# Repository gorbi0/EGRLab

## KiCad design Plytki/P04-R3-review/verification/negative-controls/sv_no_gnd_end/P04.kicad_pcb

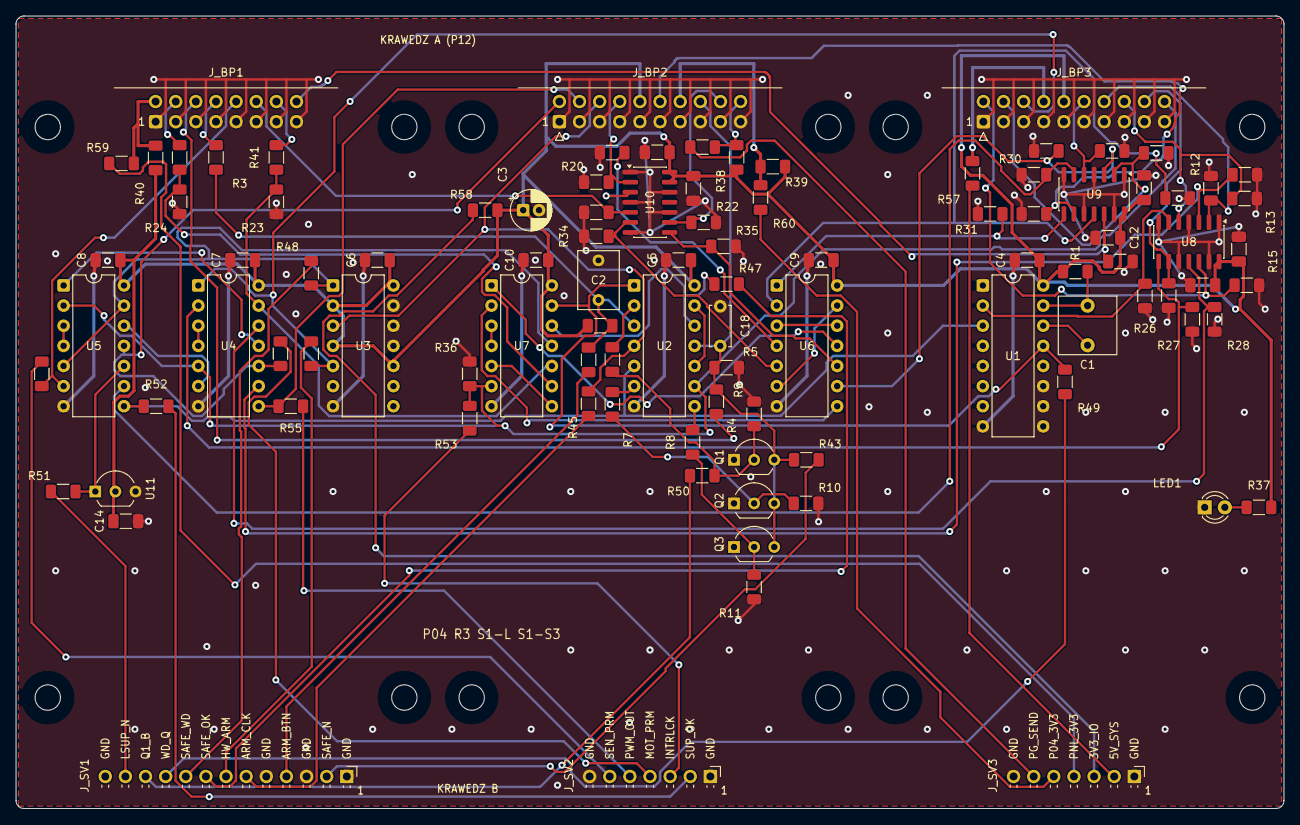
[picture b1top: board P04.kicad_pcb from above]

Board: 2 copper layers, 160.0 x 100.0 mm, 112 parts (0 on the bottom side), 86 nets.

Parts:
C1: 1u; C_WIMA_MKS2_1u100V_L7.2_W7.2_P5
C2: 1u; C_Rect_L7.2mm_W5.0mm_P5.00mm
C3: 10u; CP_Radial_D5.0mm_P2.00mm
C4, C5, C6, C7, C8, C9, C10, C11, C12, C13, C14, C15, C16, C17: 100n; C_1206_3216Metric_Pad1.33x1.80mm_HandSolder
C18: 1n; C_Disc_D5.0mm_W2.5mm_P5.00mm
H1, H2, H3, H4, H5, H6, H7, H8, H9, H10, H11, H12: M3 NPTH
J_BP1: J_BP1; IDC-Header_2x08_P2.54mm_Horizontal
J_BP2: J_BP2; IDC-Header_2x10_P2.54mm_Horizontal
J_BP3: J_BP3; IDC-Header_2x10_P2.54mm_Horizontal
J_SV1: J_SV1 SERWIS 1x13; PinHeader_1x13_P2.54mm_Horizontal
J_SV2: J_SV2 SERWIS 1x7; PinHeader_1x07_P2.54mm_Horizontal
J_SV3: J_SV3 SERWIS 1x7; PinHeader_1x07_P2.54mm_Horizontal
LED1: POWER; LED_D3.0mm
Q1, Q2, Q3: 2N3904; TO-92_Inline_Wide
R1: 220K; R_1206_3216Metric_Pad1.30x1.75mm_HandSolder
R2, R4, R6, R7, R8, R12, R13, R14, R15, R16, R17, R18, R19, R20, R21, R22, R23, R24, R25, R29, R31, R32, R33, R34, R35, R36, R43, R44: 10K; R_1206_3216Metric_Pad1.30x1.75mm_HandSolder
R3, R37, R38, R39, R41, R42, R45, R46, R47, R48, R49, R50, R51, R52, R53, R54, R55, R56, R57, R58, R59, R60, R61: 1K; R_1206_3216Metric_Pad1.30x1.75mm_HandSolder
R5, R9, R10, R11, R28, R30: 100K; R_1206_3216Metric_Pad1.30x1.75mm_HandSolder
R26, R27: 47K; R_1206_3216Metric_Pad1.30x1.75mm_HandSolder
R40: 100R; R_1206_3216Metric_Pad1.30x1.75mm_HandSolder
U1: CD74HC123E; DIP-16_W7.62mm
U2: SN74HC14N; DIP-14_W7.62mm
U3: SN74HC74N; DIP-14_W7.62mm
U4, U5, U6, U7: SN74HC08N; DIP-14_W7.62mm
U8, U9, U10: 74LVC125AD; SOIC-14_3.9x8.7mm_P1.27mm
U11: MCP100-300DI/TO; TO-92_Inline_Wide

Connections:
3V3_IO: C3.1, C4.1, C5.1, C6.1, C7.1, C8.1, C9.1, C10.1, C11.1, C12.1, C13.1, C14.1, C15.1, C16.1, C17.1, J_BP2.10, J_BP3.10, R1.1, R2.1, R37.1, R38.1, R39.1, R40.1, R58.1, U1.16, U2.14, U3.2, U3.4, U3.10, U3.14, U4.14, U5.14, U6.14, U7.14, U8.14, U9.14, U10.13, U10.14, U11.2
5V_SYS: J_BP3.8, R57.1
/ILK/MECH_KEY: U7.5, U7.8
/ILK/MECH_OK_P04: R24.1, R42.2, U7.9
/ILK/MODULES_OK: U7.3, U7.4
/ILK/OK_A: U6.3, U6.12
/ILK/OK_AB: U6.11, U7.1
/ILK/OK_B: U6.6, U6.13
/ILK/OK_C: U6.8, U7.2
/LED_PWR: LED1.2, R37.2
/OUT/ARM_BOTH: U4.3, U4.4
/OUT/MOTOR_REQ: U4.6, U5.12
/OUT/SENSOR_INTERLOCK: U5.3, U5.4
/OUT/SENSOR_KEY: U4.11, U5.1
/SERWIS/SRV_3V3_IO: J_SV3.3, R58.2
/SERWIS/SRV_5V_SYS: J_SV3.2, R57.2
/SERWIS/SRV_ARM_BUTTON_N: J_SV1.4, R44.2
/SERWIS/SRV_ARM_CLK: J_SV1.6, R45.2
/SERWIS/SRV_HW_ARMED: J_SV1.7, R46.2
/SERWIS/SRV_INTERLOCK: J_SV2.3, R53.2
/SERWIS/SRV_LOCAL_SUP_N: J_SV1.12, J_SV1.13, R51.2
/SERWIS/SRV_MOTOR_PERMIT: J_SV2.4, R54.2
/SERWIS/SRV_P04_3V3: J_SV3.5, R60.2
/SERWIS/SRV_PANEL_3V3: J_SV3.4, R59.2
/SERWIS/SRV_PG_SEND: J_SV3.6, R61.2
/SERWIS/SRV_PWM_OUT: J_SV2.5, R55.2
/SERWIS/SRV_Q1_B: J_SV1.11, R50.2
/SERWIS/SRV_SAFE_N: J_SV1.2, R43.2
/SERWIS/SRV_SAFE_OK: J_SV1.8, R47.2
/SERWIS/SRV_SAFE_WD: J_SV1.9, R48.2
/SERWIS/SRV_SENSOR_PERMIT: J_SV2.6, R56.2
/SERWIS/SRV_SUP_OK: J_SV2.2, R52.2
/SERWIS/SRV_WD_Q: J_SV1.10, R49.2
/WD/ILK_BAD: R8.1, U2.8
/WD/Q2_B: Q2.2, R7.2, R10.1
/WD/Q3_B: Q3.2, R8.2, R11.1
/WD/SAFE_OK_N: U2.10, U2.13
/WD/SUP_BAD: R7.1, U2.6
/WD/WD_BAD: R6.1, U2.2
/WD/WD_C: C1.2, U1.14
/WD/WD_RC: C1.1, R1.2, U1.15
ARM_BUTTON_N: C2.1, R2.2, R3.1, R44.1, U2.3
ARM_CLK: J_BP2.6, R45.1, U2.4, U3.3
ARM_CONTACT: J_BP1.8, R3.2
CORE_LINK: J_BP3.4, R16.1, U9.2
CORE_LINK_P04: R29.1, U6.9, U9.3
DAQ_OK: J_BP1.16, R19.1, U9.12
DAQ_OK_P04: R32.1, U6.2, U9.11
DRIVE_OK: J_BP2.8, R20.1, U10.2
DRIVE_OK_P04: R33.1, U6.4, U10.3
GND: C2.2, C3.2, C4.2, C5.2, C6.2, C7.2, C8.2, C9.2, C10.2, C11.2, C12.2, C13.2, C14.2, C15.2, C16.2, C17.2, C18.2, J_BP1.1, J_BP1.3, J_BP1.5, J_BP1.7, J_BP1.9, J_BP1.11, J_BP1.13, J_BP1.15, J_BP2.1, J_BP2.3, J_BP2.5, J_BP2.7, J_BP2.9, J_BP2.11, J_BP2.13, J_BP2.15, J_BP2.17, J_BP2.19, J_BP3.1, J_BP3.3, J_BP3.5, J_BP3.7, J_BP3.9, J_BP3.11, J_BP3.13, J_BP3.15, J_BP3.17, J_BP3.19, J_SV1.1, J_SV1.3, J_SV1.5, J_SV2.1, J_SV2.7, J_SV3.1, J_SV3.7, LED1.1, Q1.1, Q2.1, Q3.1, R5.2, R9.2, R10.2, R11.2, R12.2, R13.2, R14.2, R15.2, R16.2, R17.2, R18.2, R19.2, R20.2, R21.2, R22.2, R23.2, R24.2, R25.2, R26.2, R27.2, R28.2, R29.2, R30.2, R31.2, R32.2, R33.2, R34.2, R35.2, R36.2, U1.1, U1.8, U1.9, U1.10, U1.11, U2.7, U3.7, U3.11, U3.12, U3.13, U4.7, U5.7, U6.7, U7.7, U8.1, U8.4, U8.7, U8.10, U8.13, U9.1, U9.4, U9.7, U9.10, U9.13, U10.1, U10.4, U10.7, U10.10, U10.12, U11.3
HEARTBEAT: J_BP3.16, R13.1, U8.5
HEARTBEAT_P04: R26.1, U1.2, U8.6
HW_ARMED: J_BP3.6, R46.1, U3.5, U4.1
INTERLOCK: J_BP3.20, R36.1, R53.1, U2.9, U4.5, U5.2, U7.6
LOCAL_SUP_N: R51.1, U5.10, U11.1
MCU_ARM: J_BP3.18, R14.1, U8.9
MCU_ARM_P04: R27.1, U4.2, U8.8
MECH_OK: J_BP1.4, R42.1
MOTOR_PERMIT: J_BP2.2, R54.1, U4.10, U5.11
P04_3V3: J_BP2.14, R39.2, R60.1
PANEL_3V3: J_BP1.2, R40.2, R59.1
PG_LINK: J_BP2.18, R22.1, U10.9
PG_LINK_P04: R35.1, U6.10, U10.8
PG_SEND: J_BP2.20, R38.2, R61.1
PSU_OK: J_BP2.12, R18.1, U9.9
PSU_OK_P04: R31.1, U6.1, U9.8
PWM: J_BP3.14, R12.1, U8.2
PWM_OUT: J_BP2.4, R55.1, U4.8
PWM_P04: R25.1, U4.9, U8.3
Q1_B: Q1.2, R6.2, R9.1, R50.1
SAFE_N: C18.1, J_BP2.16, Q1.3, Q2.3, Q3.3, R4.2, R5.1, R43.1, U2.11
SAFE_OK: R47.1, U2.12, U7.12
SAFE_WD: R48.1, U3.1, U5.5, U5.13, U7.11
SENSOR_ENABLE: J_BP3.2, R15.1, U8.12
SENSOR_ENABLE_P04: R28.1, U4.12, U8.11
SENSOR_OK: J_BP1.12, R21.1, U10.5
SENSOR_OK_P04: R34.1, U6.5, U10.6
SENSOR_PERMIT: J_BP1.10, R56.1, U5.6
STOP_NC_OUT: J_BP1.6, R4.1
SUP_N_OUT: J_BP3.12, R17.1, U9.5
SUP_N_P04: R30.1, U5.9, U9.6
SUP_OK: R52.1, U1.3, U2.5, U5.8
TEST_KEY: J_BP1.14, R41.1
TEST_KEY_P04: R23.1, R41.2, U4.13, U7.10
WD_Q: R49.1, U1.13, U2.1, U7.13
